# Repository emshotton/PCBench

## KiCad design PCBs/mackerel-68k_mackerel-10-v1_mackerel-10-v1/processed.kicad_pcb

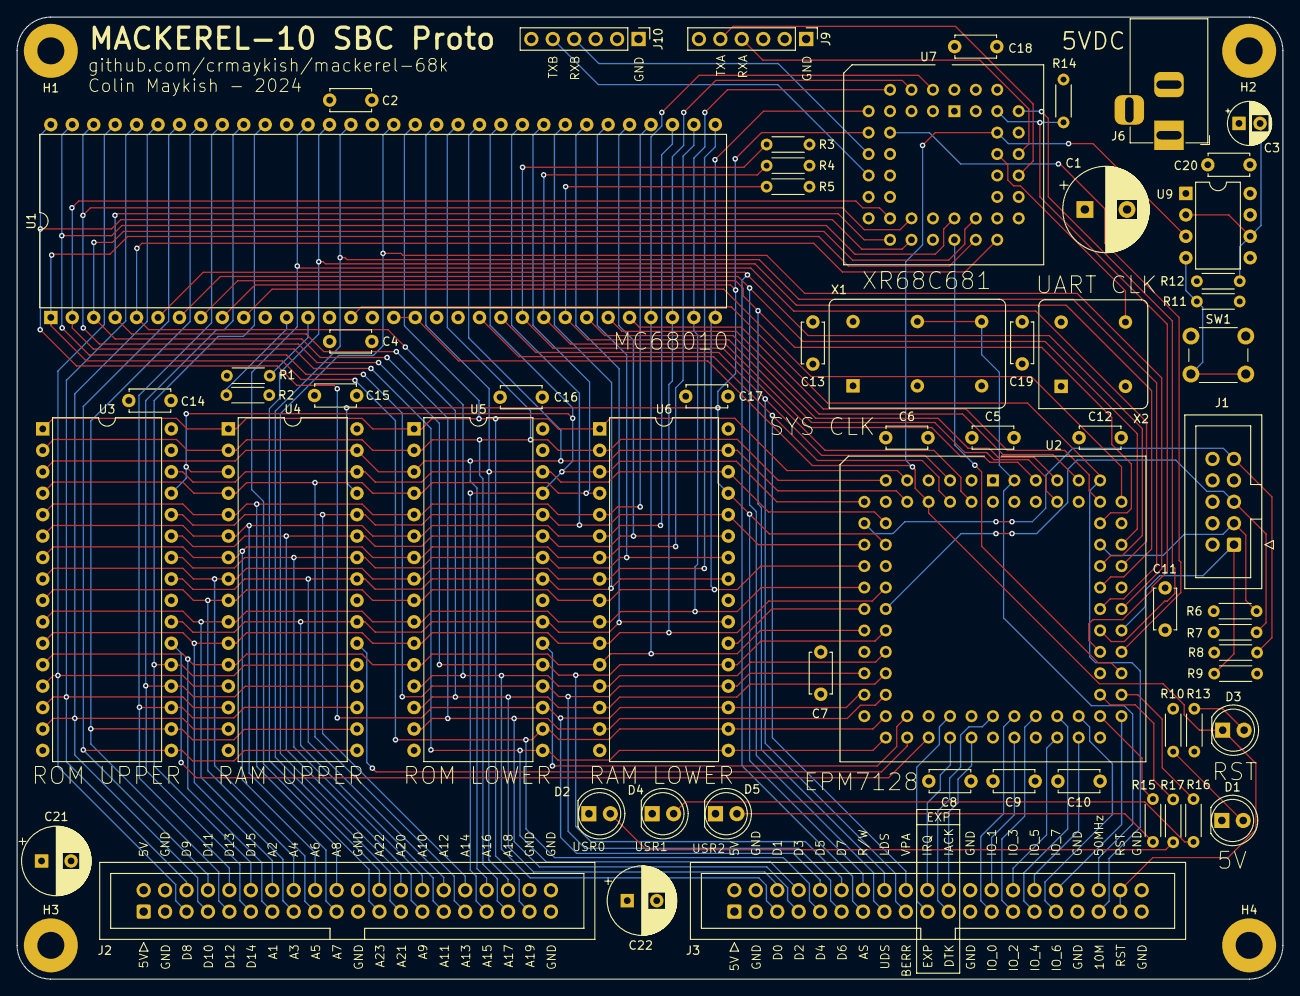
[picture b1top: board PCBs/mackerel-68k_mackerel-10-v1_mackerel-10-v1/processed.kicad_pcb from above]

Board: 4 copper layers, 150.0 x 114.0 mm, 65 parts (0 on the bottom side), 98 nets.

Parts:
C1: 1000uF; CP_Radial_D10.0mm_P5.00mm
C2, C4, C5, C6, C7, C8, C9, C10, C11, C12, C13, C14, C15, C16, C17, C18, C19, C20: 0.1uF; C_Disc_D4.7mm_W2.5mm_P5.00mm
C3: C_Polarized; CP_Radial_D5.0mm_P2.50mm
C21, C22: 1000uF; CP_Radial_D8.0mm_P3.50mm
D1, D2, D3, D4, D5: LED; LED_D5.0mm
H1, H2, H3, H4: MountingHole_Pad; MountingHole_3.2mm_M3_Pad
J1: Conn_02x05_Odd_Even; IDC-Header_2x05_P2.54mm_Vertical
J2, J3: Conn_02x20_Odd_Even; IDC-Header_2x20_P2.54mm_Vertical
J6: Barrel_Jack_MountingPin; BarrelJack_Horizontal
J9, J10: Conn_01x06; PinHeader_1x06_P2.54mm_Vertical
R1, R2, R3, R4, R5, R6, R7, R8, R9, R10, R11, R12, R13, R14, R15, R16, R17: R; R_Axial_DIN0204_L3.6mm_D1.6mm_P5.08mm_Horizontal
SW1: SW_Push; SW_PUSH_6mm_H5mm
U1: 68010D; DIP-64_W22.86mm
U2: PLCC-84_THT-Socket
U3, U5: SST39SF040; DIP-32_W15.24mm
U4, U6: AS6C4008-55PCN; DIP-32_W15.24mm
U7: XR68C681; PLCC-44_THT-Socket
U9: NE555P; DIP-8_W7.62mm
X1: 50MHz; Oscillator_DIP-14
X2: 3.6864MHz; Oscillator_DIP-8

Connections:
+5V: C1.1, C2.1, C3.1, C4.1, C5.1, C6.1, C7.1, C8.1, C9.1, C10.1, C11.1, C12.1, C13.1, C14.1, C15.1, C16.1, C17.1, C18.1, C19.1, C20.1, C21.1, C22.1, J1.4, J2.1, J2.2, J3.1, J3.2, J6.1, R1.1, R2.1, R3.1, R4.1, R5.1, R6.1, R7.1, R8.1, R10.1, R11.1, R13.1, R14.2, U1.14 (VCC), U1.49 (VCC), U2.3 (VCCINT), U2.13 (VCCIO), U2.26 (VCCIO), U2.38 (VCCIO), U2.43 (VCCINT), U2.53 (VCCIO), U2.66 (VCCIO), U2.78 (VCCIO), U3.31 (PGM), U3.32 (VCC), U4.32 (VCC), U5.31 (PGM), U5.32 (VCC), U6.32 (VCC), U7.44 (VCC), U9.8 (VCC), X1.14 (Vcc), X2.8 (Vcc)
A1: J2.13, U1.29 (A1), U2.24 (IO), U3.12 (A0), U4.12 (A0), U5.12 (A0), U6.12 (A0), U7.2 (A1)
A2: J2.14, U1.30 (A2), U2.21 (IO), U3.11 (A1), U4.11 (A1), U5.11 (A1), U6.11 (A1), U7.4 (A2)
A3: J2.15, U1.31 (A3), U2.20 (IO), U3.10 (A2), U4.10 (A2), U5.10 (A2), U6.10 (A2), U7.6 (A3)
A4: J2.16, U1.32 (A4), U2.18 (IO), U3.9 (A3), U4.9 (A3), U5.9 (A3), U6.9 (A3), U7.7 (A4)
A5: J2.17, U1.33 (A5), U3.8 (A4), U4.8 (A4), U5.8 (A4), U6.8 (A4)
A6: J2.18, U1.34 (A6), U3.7 (A5), U4.7 (A5), U5.7 (A5), U6.7 (A5)
A7: J2.19, U1.35 (A7), U3.6 (A6), U4.6 (A6), U5.6 (A6), U6.6 (A6)
A8: J2.20, U1.36 (A8), U3.5 (A7), U4.5 (A7), U5.5 (A7), U6.5 (A7)
A9: J2.27, U1.37 (A9), U3.27 (A8), U4.27 (A8), U5.27 (A8), U6.27 (A8)
A10: J2.28, U1.38 (A10), U3.26 (A9), U4.26 (A9), U5.26 (A9), U6.26 (A9)
A11: J2.29, U1.39 (A11), U3.23 (A10), U4.23 (A10), U5.23 (A10), U6.23 (A10)
A12: J2.30, U1.40 (A12), U3.25 (A11), U4.25 (A11), U5.25 (A11), U6.25 (A11)
A13: J2.31, U1.41 (A13), U3.4 (A12), U4.4 (A12), U5.4 (A12), U6.4 (A12)
A14: J2.32, U1.42 (A14), U2.16 (IO), U3.28 (A13), U4.28 (A13), U5.28 (A13), U6.28 (A13)
A15: J2.33, U1.43 (A15), U2.12 (IO), U3.29 (A14), U4.3 (A14), U5.29 (A14), U6.3 (A14)
A16: J2.34, U1.44 (A16), U2.10 (IO), U3.3 (A15), U4.31 (A15), U5.3 (A15), U6.31 (A15)
A17: J2.35, U1.45 (A17), U2.11 (IO), U3.2 (A16), U4.2 (A16), U5.2 (A16), U6.2 (A16)
A18: J2.36, U1.46 (A18), U2.15 (IO), U3.30 (A17), U4.30 (A17), U5.30 (A17), U6.30 (A17)
A19: J2.37, U1.47 (A19), U2.9 (IO), U3.1 (A18), U4.1 (A18), U5.1 (A18), U6.1 (A18)
A20: J2.26, U1.48 (A20), U2.64 (IO)
A21: J2.25, U1.50 (A21), U2.65 (IO)
A22: J2.24, U1.51 (A22), U2.67 (IO)
A23: J2.23, U1.52 (A23), U2.68 (IO)
CLK_CPU: J3.35, U1.15 (CLK), U2.75 (IO)
CLK_SRC: J3.36, U2.83 (GCLK1), X1.8 (OUT)
D0: J3.5, U1.5 (D0), U2.27 (IO), U5.13 (D0), U6.13 (DQ0), U7.28 (D0)
D1: J3.6, U1.4 (D1), U2.29 (IO), U5.14 (D1), U6.14 (DQ1), U7.18 (D1)
D2: J3.7, U1.3 (D2), U2.31 (IO), U5.15 (D2), U6.15 (DQ2), U7.27 (D2)
D3: J3.8, U1.2 (D3), U2.33 (IO), U5.17 (D3), U6.17 (DQ3), U7.19 (D3)
D4: J3.9, U1.1 (D4), U2.34 (IO), U5.18 (D4), U6.18 (DQ4), U7.26 (D4)
D5: J3.10, U1.64 (D5), U2.30 (IO), U5.19 (D5), U6.19 (DQ5), U7.20 (D5)
D6: J3.11, U1.63 (D6), U2.28 (IO), U5.20 (D6), U6.20 (DQ6), U7.25 (D6)
D7: J3.12, U1.62 (D7), U2.25 (IO), U5.21 (D7), U6.21 (DQ7), U7.21 (D7)
D8: J2.5, U1.61 (D8), U3.13 (D0), U4.13 (DQ0)
D9: J2.6, U1.60 (D9), U3.14 (D1), U4.14 (DQ1)
D10: J2.7, U1.59 (D10), U3.15 (D2), U4.15 (DQ2)
D11: J2.8, U1.58 (D11), U3.17 (D3), U4.17 (DQ3)
D12: J2.9, U1.57 (D12), U3.18 (D4), U4.18 (DQ4)
D13: J2.10, U1.56 (D13), U3.19 (D5), U4.19 (DQ5)
D14: J2.11, U1.55 (D14), U3.20 (D6), U4.20 (DQ6)
D15: J2.12, U1.54 (D15), U3.21 (D7), U4.21 (DQ7)
FC0: U1.28 (FC0), U2.76 (IO)
FC1: U1.27 (FC1), U2.77 (IO)
FC2: U1.26 (FC2), U2.79 (IO)
GND: C1.2, C2.2, C4.2, C5.2, C6.2, C7.2, C8.2, C9.2, C10.2, C11.2, C12.2, C13.2, C14.2, C15.2, C16.2, C17.2, C18.2, C19.2, C20.2, C21.2, C22.2, D1.1 (K), D2.1 (K), D4.1 (K), D5.1 (K), H1.1, H2.1, H3.1, H4.1, J1.2, J1.10, J2.3, J2.4, J2.21, J2.22, J2.38, J2.39, J2.40, J3.3, J3.4, J3.23, J3.24, J3.33, J3.34, J3.39, J3.40, J6.2, J9.1, J10.1, R9.2, R12.2, SW1.1, U1.16 (GND), U1.53 (GND), U2.1 (GCLRn), U2.2 (OE2/GCLK2), U2.7 (GND), U2.19 (GND), U2.32 (GND), U2.42 (GND), U2.47 (GND), U2.59 (GND), U2.72 (GND), U2.82 (GND), U2.84 (OE1), U3.16 (GND), U3.24 (OE), U4.16 (VSS), U4.24 (OE#), U5.16 (GND), U5.24 (OE), U6.16 (VSS), U6.24 (OE#), U7.3 (IP3), U7.5 (IP1), U7.8 (IP0), U7.22 (GND), U7.40 (IP2), U7.42 (IP5), U7.43 (IP4), U9.1 (GND), X1.7 (GND), X2.4 (GND)
GPIO_0: J3.25, U2.46 (IO)
GPIO_1: J3.26, U2.45 (IO)
GPIO_2: J3.27, U2.48 (IO)
GPIO_3: J3.28, U2.49 (IO)
GPIO_4: J3.29, U2.50 (IO)
GPIO_5: J3.30, U2.51 (IO)
GPIO_6: J3.31, U2.52 (IO)
GPIO_7: J3.32, U2.54 (IO)
unnamed: D1.2 (A), R10.2
unnamed: D3.2 (A), R13.2
unnamed: R15.1, U2.55 (IO)
unnamed: R16.1, U2.56 (IO)
unnamed: R17.1, U2.57 (IO)
unnamed: R2.2, U1.12 (BGACK)
unnamed: R1.2, U1.13 (BR)
unnamed: U7.36 (X1/CLK), X2.5 (OUT)
unnamed: R11.2, SW1.2, U9.4 (R)
unnamed: C3.2, R12.1, U9.2 (TR), U9.6 (THR)
RXA: J9.4, U7.35 (RXDA)
RXB: J10.4, U7.11 (RXDB)
R/W: J3.14, U1.9 (R/W), U2.17 (IO), U4.29 (WE#), U6.29 (WE#), U7.9 (/RW)
TCK: J1.1, R9.1, U2.62 (TCK)
TDI: J1.9, R8.2, U2.14 (TDI)
TDO: J1.3, R6.2, U2.71 (TDO)
TMS: J1.5, R7.2, U2.23 (TMS)
TXA: J9.5, U7.33 (TXDA)
TXB: J10.5, U7.13 (TXDB)
USR0: D5.2 (A), R15.2
USR1: D4.2 (A), R16.2
USR2: D2.2 (A), R17.2
/AS: J3.13, U1.6 (AS), U2.69 (IO)
/BERR: J3.17, U1.22 (BERR), U2.5 (IO)
/DTACK: U1.10 (DTACK), U2.74 (IO)
/DTACK_DUART: U2.60 (IO), U7.10 (/DTACK)
/DTACK_EXP: J3.21, U2.44 (IO)
/DUART: U2.63 (IO), U7.39 (CS)
/EXP: J3.19, U2.40 (IO)
/IACK_DUART: R14.1, U2.61 (IO), U7.41 (/IACK)
/IACK_EXP: J3.22, U2.41 (IO)
/IPL0: R5.2, U1.25 (IPL0), U2.80 (IO)
/IPL1: R4.2, U1.24 (IPL1), U2.81 (IO)
/IPL2: R3.2, U1.23 (IPL2), U2.4 (IO)
/IRQ_DUART: U2.58 (IO), U7.24 (INTR)
/IRQ_EXP: J3.20, U2.39 (IO)
/LDS: J3.16, U1.8 (LDS), U2.73 (IO)
/RESET: D3.1 (K), J3.37, J3.38, U1.17 (HALT), U1.18 (RESET), U2.8 (IO), U7.38 (/RESET), U9.3 (Q)
/ROM_LOWER: U2.36 (IO), U5.22 (CE)
/ROM_UPPER: U2.37 (IO), U3.22 (CE)
/SRAM_LOWER: U2.22 (IO), U6.22 (CE#)
/SRAM_UPPER: U2.35 (IO), U4.22 (CE#)
/UDS: J3.15, U1.7 (UDS), U2.70 (IO)
/VPA: J3.18, U1.21 (VPA), U2.6 (IO)

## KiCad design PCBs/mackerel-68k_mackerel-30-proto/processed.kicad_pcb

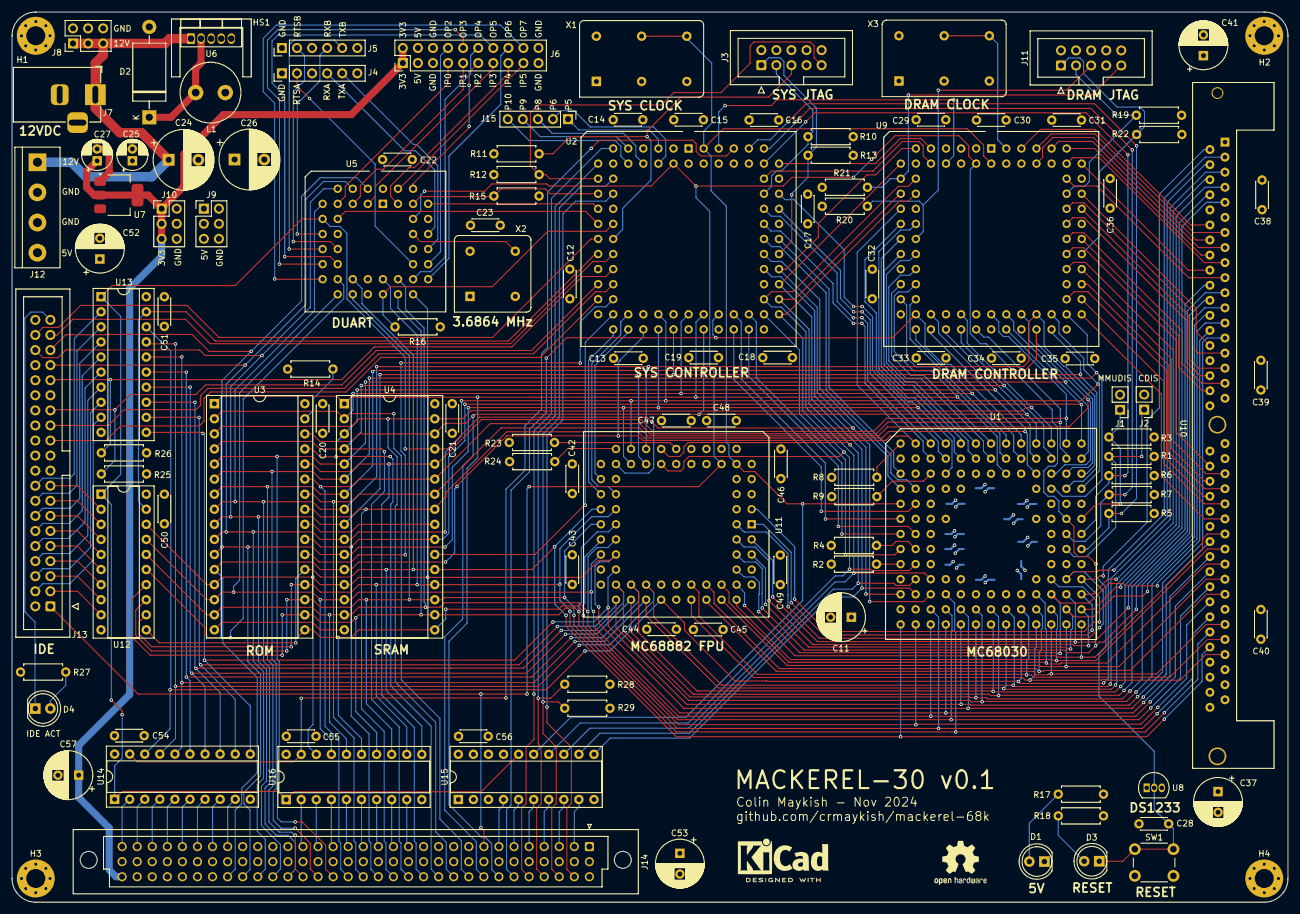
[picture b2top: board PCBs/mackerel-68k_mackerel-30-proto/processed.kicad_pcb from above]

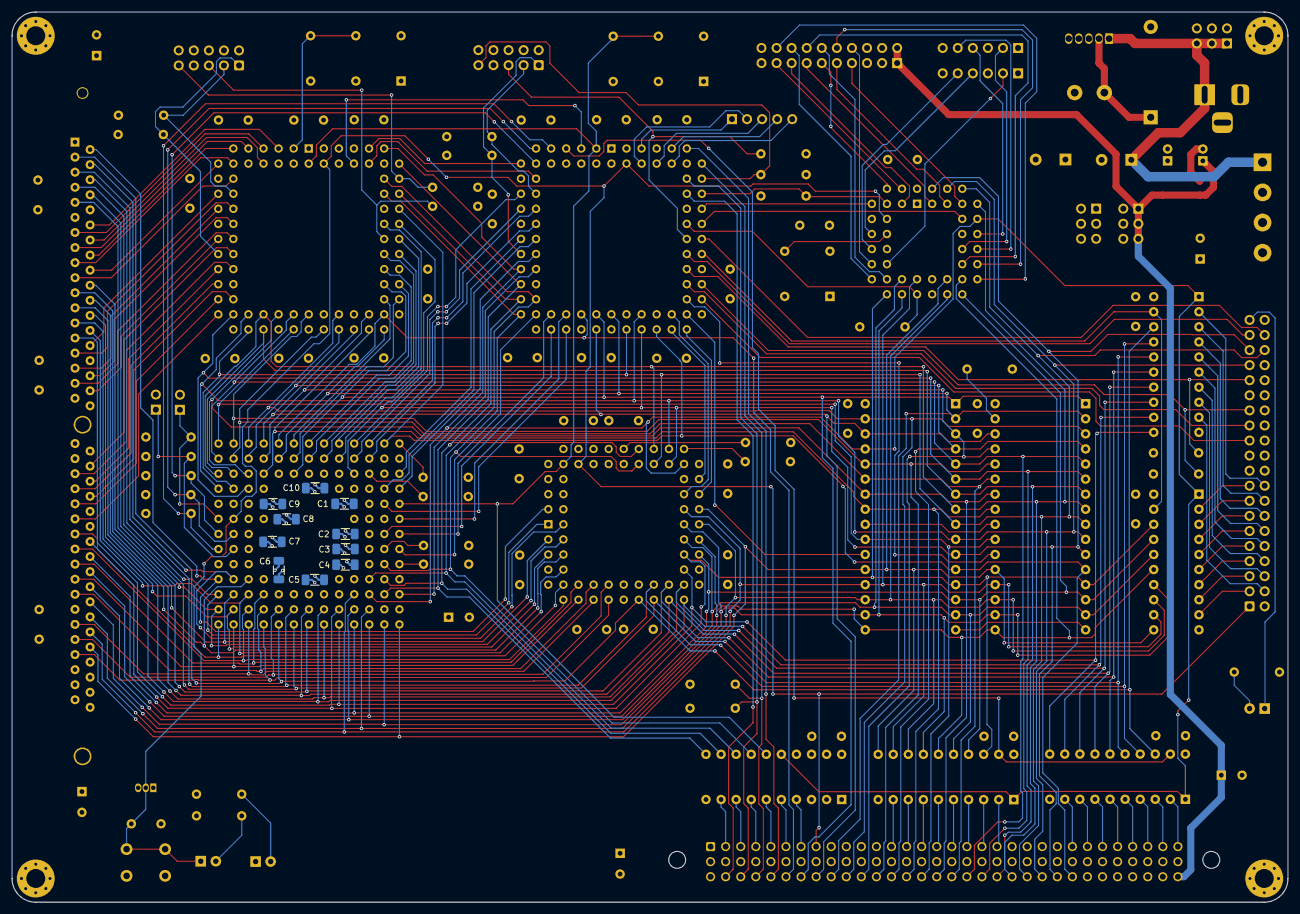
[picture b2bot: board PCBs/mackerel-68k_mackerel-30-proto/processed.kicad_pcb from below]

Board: 4 copper layers, 215.0 x 150.0 mm, 131 parts (10 on the bottom side), 217 nets.

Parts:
C1, C2, C3, C4, C5, C6, C7, C8, C9, C10: 0.1uF; C_1206_3216Metric_Pad1.33x1.80mm_HandSolder
C11, C37, C41, C52, C53, C57: 470uF; CP_Radial_D8.0mm_P3.50mm
C12, C13, C14, C15, C16, C17, C18, C19, C20, C21, C22, C23, C29, C30, C31, C32, C33, C34, C35, C36, C38, C39, C40, C42, C43, C44, C45, C46, C47, C48, C49, C54, C55, C56: 0.1uF; C_Disc_D4.3mm_W1.9mm_P5.00mm
C24, C26: 1000uF; CP_Radial_D10.0mm_P5.00mm
C25, C27: 10uF; CP_Radial_D5.0mm_P2.00mm
C28: 0.01uF; C_Disc_D4.3mm_W1.9mm_P5.00mm
C50, C51: C; C_Disc_D4.3mm_W1.9mm_P5.00mm
D1, D3, D4: LED; LED_D5.0mm
D2: 1N5822; D_DO-27_P15.24mm_Horizontal
H1, H2, H3, H4: MountingHole_Pad; MountingHole_3.2mm_M3_Pad_Via
HS1: Heatsink; Heatsink_Stonecold_HS-S02_13.21x9.53mm
J1, J2: Conn_01x02; PinHeader_1x02_P2.54mm_Vertical
J3, J11: Conn_02x05_Odd_Even; IDC-Header_2x05_P2.54mm_Vertical
J4, J5: Conn_01x06; PinHeader_1x06_P2.54mm_Vertical
J6: Conn_02x10_Odd_Even; PinHeader_2x10_P2.54mm_Vertical
J7: Barrel_Jack_MountingPin; BarrelJack_Horizontal
J8, J9, J10: Conn_02x03_Odd_Even; PinHeader_2x03_P2.54mm_Vertical
J12: Screw_Terminal_01x04; TerminalBlock_bornier-4_P5.08mm
J13: Conn_02x20_Odd_Even; IDC-Header_2x20_P2.54mm_Vertical
J14: DIN41612_03x32_ABC; DIN41612_C_3x32_Female_Vertical_THT
J15: Conn_01x05; PinHeader_1x05_P2.54mm_Vertical
L1: 100uH; L_Radial_D10.0mm_P5.00mm_Fastron_07M
R1, R2, R3, R4, R5, R6, R7, R8, R9, R14, R23, R24, R25, R26, R28, R29: 4k7; R_Axial_DIN0207_L6.3mm_D2.5mm_P7.62mm_Horizontal
R10, R11, R12, R13, R15, R16, R19, R20, R21, R22: R; R_Axial_DIN0207_L6.3mm_D2.5mm_P7.62mm_Horizontal
R17, R18: 1k; R_Axial_DIN0207_L6.3mm_D2.5mm_P7.62mm_Horizontal
R27: 470; R_Axial_DIN0207_L6.3mm_D2.5mm_P7.62mm_Horizontal
SW1: SW_Push; SW_PUSH_6mm_H5mm
U1: MC68030RC; PGA169
U2, U9: EPM7128; PLCC-84_THT-Socket
U3: SST39SF040; DIP-32_W15.24mm_Socket
U4: AS6C4008-55PCN; DIP-32_W15.24mm_Socket
U5: XR68C681; PLCC-44_THT-Socket
U6: LM2576T-5; TO-220-5_Vertical
U7: AMS1117-3.3; SOT-223-3_TabPin2
U8: DS1233; TO-92L_Inline
U10: SIMM72; SIMM-72
U11: MC68882; PLCC-68_THT-Socket
U12, U13, U14, U15, U16: 74HC245; DIP-20_W7.62mm_Socket
X1, X3: CXO_DIP14; Oscillator_DIP-14
X2: 3.6864MHz; Oscillator_DIP-8

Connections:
+3.3V: C27.1, C57.1, J6.1, J6.2, J10.1, J10.3, J10.5, J14.c32, U7.2 (VO)
+5V: C1.1, C2.1, C3.1, C4.1, C5.1, C6.1, C7.1, C8.1, C9.1, C10.1, C11.1, C12.1, C13.1, C14.1, C15.1, C16.1, C17.1, C18.1, C19.1, C20.1, C21.1, C22.1, C23.1, C25.1, C26.1, C29.1, C30.1, C31.1, C32.1, C33.1, C34.1, C35.1, C36.1, C37.1, C38.1, C39.1, C40.1, C41.1, C42.1, C43.1, C44.1, C45.1, C46.1, C47.1, C48.1, C49.1, C50.1, C51.1, C52.1, C53.1, C54.1, C55.1, C56.1, J3.4, J6.3, J6.4, J9.1, J9.3, J9.5, J11.4, J12.4, J14.a1, J14.c1, L1.2, R1.1, R2.1, R3.1, R4.1, R5.1, R6.1, R7.1, R8.1, R9.1, R10.1, R11.1, R12.1, R14.1, R15.2, R16.2, R17.1, R18.1, R19.1, R20.1, R21.1, R23.1, R24.1, R27.1, R28.2, R29.2, U1.C6 (VCC), U1.D4 (VCC), U1.D10 (VCC), U1.F2 (VCC), U1.F11 (VCC), U1.H3 (VCC), U1.H11 (VCC), U1.K4 (VCC), U1.K10 (VCC), U1.L6 (VCC), U2.3 (VCCINT), U2.13 (VCCIO), U2.26 (VCCIO), U2.38 (VCCIO), U2.43 (VCCINT), U2.53 (VCCIO), U2.66 (VCCIO), U2.78 (VCCIO), U3.32 (VCC), U4.32 (VCC), U5.44 (VCC), U6.4 (FB), U7.3 (VI), U8.3 (VCC), U9.3 (VCCINT), U9.13 (VCCIO), U9.26 (VCCIO), U9.38 (VCCIO), U9.43 (VCCINT), U9.53 (VCCIO), U9.66 (VCCIO), U9.78 (VCCIO), U10.10 (VCC), U10.30 (VCC), U10.59 (VCC), U11.10 (VCC), U11.16 (VCC), U11.17 (VCC), U11.27 (VCC), U11.43 (VCC), U11.52 (VCC), U11.53 (VCC), U11.61 (VCC), U12.20 (VCC), U13.20 (VCC), U14.20 (VCC), U15.20 (VCC), U16.20 (VCC), X1.14 (Vcc), X2.8 (Vcc), X3.14 (Vcc)
+12V: C24.1, J7.1, J8.1, J8.3, J8.5, J12.1, U6.1 (VIN)
A0: J14.c25, U1.A2 (A0), U2.37 (IO), U3.12 (A0), U4.12 (A0), U9.18 (IO)
A1: J13.35, J14.c24, U1.C4 (A1), U2.39 (IO), U3.11 (A1), U4.11 (A1), U5.2 (A1), U9.20 (IO), U11.25 (A1)
A2: J13.33, J14.c23, U1.D13 (A2), U2.40 (IO), U3.10 (A2), U4.10 (A2), U5.4 (A2), U9.52 (IO), U11.24 (A2)
A3: J13.36, J14.c22, U1.D12 (A3), U2.41 (IO), U3.9 (A3), U4.9 (A3), U5.6 (A3), U9.51 (IO), U11.23 (A3)
A4: J14.c21, U1.C13 (A4), U3.8 (A4), U4.8 (A4), U5.7 (A4), U9.50 (IO), U11.22 (A4)
A5: J14.c20, U1.C12 (A5), U3.7 (A5), U4.7 (A5), U9.49 (IO)
A6: J14.c19, U1.D11 (A6), U3.6 (A6), U4.6 (A6), U9.55 (IO)
A7: J14.c18, U1.B13 (A7), U3.5 (A7), U4.5 (A7), U9.46 (IO)
A8: J14.c17, U1.B12 (A8), U3.27 (A8), U4.27 (A8), U9.41 (IO)
A9: J14.c16, U1.C11 (A9), U3.26 (A9), U4.26 (A9), U9.48 (IO)
A10: J14.c15, U1.A13 (A10), U3.23 (A10), U4.23 (A10), U9.45 (IO)
A11: J14.c14, U1.C10 (A11), U3.25 (A11), U4.25 (A11), U9.35 (IO)
A12: J14.c13, U1.B11 (A12), U3.4 (A12), U4.4 (A12), U9.39 (IO)
A13: J14.c12, U1.A12 (A13), U3.28 (A13), U4.28 (A13), U9.44 (IO)
A14: J14.c11, U1.B10 (A14), U3.29 (A14), U4.3 (A14), U9.36 (IO)
A15: J14.c10, U1.A11 (A15), U3.3 (A15), U4.31 (A15), U9.40 (IO)
A16: J14.c9, U1.B9 (A16), U2.44 (IO), U3.2 (A16), U4.2 (A16), U9.33 (IO)
A17: J14.c8, U1.A10 (A17), U2.45 (IO), U3.30 (A17), U4.30 (A17), U9.37 (IO)
A18: J14.c7, U1.C8 (A18), U2.46 (IO), U3.1 (A18), U4.1 (A18), U9.29 (IO)
A19: J14.c6, U1.A9 (A19), U2.48 (IO), U9.34 (IO)
A20: U1.B8 (A20), U9.30 (IO)
A21: U1.A8 (A21), U9.31 (IO)
A22: U1.B7 (A22), U9.27 (IO)
A23: U1.A7 (A23), U9.28 (IO)
A24: U1.A6 (A24), U9.25 (IO)
A25: U1.B6 (A25), U9.24 (IO)
A26: U1.A5 (A26), U9.22 (IO)
A27: U1.B5 (A27), U9.21 (IO)
A28: U1.A4 (A28), U2.70 (IO)
A29: U1.B4 (A29), U2.68 (IO)
A30: U1.A3 (A30), U2.69 (IO)
A31: U1.B3 (A31), U2.67 (IO)
CLK_CPU: U1.E1 (CLK), U2.83 (GCLK1), U9.2 (OE2/GCLK2), U11.11 (CLK), U15.15 (B3), X1.8 (OUT)
CLK_DRAM: U9.83 (GCLK1), X3.8 (OUT)
CS_EXP: J14.c5, U2.11 (IO)
D0: U1.K13 (D0), U10.2 (D0), U11.3 (D0)
D1: U1.K12 (D1), U10.4 (D1), U11.2 (D1)
D2: U1.L13 (D2), U10.6 (D2), U11.1 (D2)
D3: U1.M13 (D3), U10.8 (D3), U11.68 (D3)
D4: U1.L12 (D4), U10.20 (D4), U11.67 (D4)
D5: U1.K11 (D5), U10.22 (D5), U11.66 (D5)
D6: U1.M12 (D6), U10.24 (D6), U11.65 (D6)
D7: U1.L11 (D7), U10.26 (D7), U11.64 (D7)
D8: U1.N13 (D8), U10.49 (D8), U11.62 (D8)
D9: U1.M11 (D9), U10.51 (D9), U11.60 (D9)
D10: U1.L10 (D10), U10.53 (D10), U11.59 (D10)
D11: U1.N12 (D11), U10.55 (D11), U11.58 (D11)
D12: U1.M10 (D12), U10.57 (D12), U11.57 (D12)
D13: U1.N11 (D13), U10.61 (D13), U11.56 (D13)
D14: U1.M9 (D14), U10.63 (D14), U11.55 (D14)
D15: U1.N10 (D15), U10.65 (D15), U11.54 (D15)
D16: U1.N9 (D16), U10.3 (D16), U11.50 (D16), U13.18 (B0), U14.18 (B0)
D17: U1.M8 (D17), U10.5 (D17), U11.49 (D17), U13.17 (B1), U14.17 (B1)
D18: U1.N8 (D18), U10.7 (D18), U11.48 (D18), U13.16 (B2), U14.16 (B2)
D19: U1.N7 (D19), U10.9 (D19), U11.47 (D19), U13.15 (B3), U14.15 (B3)
D20: U1.M7 (D20), U10.21 (D20), U11.46 (D20), U13.14 (B4), U14.14 (B4)
D21: U1.N6 (D21), U10.23 (D21), U11.45 (D21), U13.13 (B5), U14.13 (B5)
D22: U1.M6 (D22), U10.25 (D22), U11.44 (D22), U13.12 (B6), U14.12 (B6)
D23: U1.N5 (D23), U10.27 (D23), U11.42 (D23), U13.11 (B7), U14.11 (B7)
D24: U1.M5 (D24), U3.13 (D0), U4.13 (DQ0), U5.28 (D0), U10.50 (D24), U11.40 (D24), U12.18 (B0), U16.18 (B0)
D25: U1.N4 (D25), U3.14 (D1), U4.14 (DQ1), U5.18 (D1), U10.52 (D25), U11.39 (D25), U12.17 (B1), U16.17 (B1)
D26: U1.N3 (D26), U3.15 (D2), U4.15 (DQ2), U5.27 (D2), U10.54 (D26), U11.38 (D26), U12.16 (B2), U16.16 (B2)
D27: U1.M4 (D27), U3.17 (D3), U4.17 (DQ3), U5.19 (D3), U10.56 (D27), U11.37 (D27), U12.15 (B3), U16.15 (B3)
D28: U1.N2 (D28), U3.18 (D4), U4.18 (DQ4), U5.26 (D4), U10.58 (D28), U11.36 (D28), U12.14 (B4), U16.14 (B4)
D29: U1.M3 (D29), U3.19 (D5), U4.19 (DQ5), U5.20 (D5), U10.60 (D29), U11.35 (D29), U12.13 (B5), U16.13 (B5)
D30: U1.L4 (D30), U3.20 (D6), U4.20 (DQ6), U5.25 (D6), U10.62 (D30), U11.34 (D30), U12.12 (B6), U16.12 (B6)
D31: U1.N1 (D31), U3.21 (D7), U4.21 (DQ7), U5.21 (D7), U10.64 (D31), U11.33 (D31), U12.11 (B7), U16.11 (B7)
DRAM_A0: U9.81 (IO), U10.12 (A0)
DRAM_A1: U9.79 (IO), U10.13 (A1)
DRAM_A2: U9.80 (IO), U10.14 (A2)
DRAM_A3: U9.77 (IO), U10.15 (A3)
DRAM_A4: U9.75 (IO), U10.16 (A4)
DRAM_A5: U9.76 (IO), U10.17 (A5)
DRAM_A6: U9.74 (IO), U10.18 (A6)
DRAM_A7: U9.70 (IO), U10.28 (A7)
DRAM_A8: U9.68 (IO), U10.31 (A8)
DRAM_A9: U9.67 (IO), U10.32 (A9)
DRAM_A10: U9.73 (IO), U10.19 (A10)
DRAM_A11: U9.69 (IO), U10.29 (A11)
DRAM_WR: U9.54 (IO), U10.47 (/WE)
DTACK_EXP: J14.c4, R28.1, U2.12 (IO)
EXP_AS: J14.a5, U15.6 (A4)
EXP_CLK: J14.a6, U15.5 (A3)
EXP_D16: J14.a32, U14.2 (A0)
EXP_D17: J14.a31, U14.3 (A1)
EXP_D18: J14.a30, U14.4 (A2)
EXP_D19: J14.a29, U14.5 (A3)
EXP_D20: J14.a28, U14.6 (A4)
EXP_D21: J14.a27, U14.7 (A5)
EXP_D22: J14.a26, U14.8 (A6)
EXP_D23: J14.a25, U14.9 (A7)
EXP_D24: J14.a20, U16.2 (A0)
EXP_D25: J14.a19, U16.3 (A1)
EXP_D26: J14.a18, U16.4 (A2)
EXP_D27: J14.a17, U16.5 (A3)
EXP_D28: J14.a16, U16.6 (A4)
EXP_D29: J14.a15, U16.7 (A5)
EXP_D30: J14.a14, U16.8 (A6)
EXP_D31: J14.a13, U16.9 (A7)
EXP_DS: J14.a3, U15.8 (A6)
EXP_RW: J14.a7, U15.4 (A2)
EXP_SIZ0: J14.a2, U15.9 (A7)
EXP_SIZ1: J14.a4, U15.7 (A5)
FC0: U1.D2 (FC0), U2.65 (IO)
FC1: U1.C1 (FC1), U2.64 (IO)
FC2: U1.D1 (FC2), U2.63 (IO)
GND: C1.2, C2.2, C3.2, C4.2, C5.2, C6.2, C7.2, C8.2, C9.2, C10.2, C11.2, C12.2, C13.2, C14.2, C15.2, C16.2, C17.2, C18.2, C19.2, C20.2, C21.2, C22.2, C23.2, C24.2, C25.2, C26.2, C27.2, C28.2, C29.2, C30.2, C31.2, C32.2, C33.2, C34.2, C35.2, C36.2, C37.2, C38.2, C39.2, C40.2, C41.2, C42.2, C43.2, C44.2, C45.2, C46.2, C47.2, C48.2, C49.2, C50.2, C51.2, C52.2, C53.2, C54.2, C55.2, C56.2, C57.2, D1.1 (K), D2.2 (A), H1.1, H2.1, H3.1, H4.1, J1.2, J2.2, J3.2, J3.10, J4.1, J5.1, J6.5, J6.6, J6.19, J6.20, J7.2, J8.2, J8.4, J8.6, J9.2, J9.4, J9.6, J10.2, J10.4, J10.6, J11.2, J11.10, J12.2, J12.3, J13.2, J13.19, J13.22, J13.24, J13.26, J13.30, J13.40, J14.b1, J14.b2, J14.b3, J14.b4, J14.b5, J14.b6, J14.b7, J14.b8, J14.b9, J14.b10, J14.b11, J14.b12, J14.b13, J14.b14, J14.b15, J14.b16, J14.b17, J14.b18, J14.b19, J14.b20, J14.b21, J14.b22, J14.b23, J14.b24, J14.b25, J14.b26, J14.b27, J14.b28, J14.b29, J14.b30, J14.b31, J14.b32, R13.2, R22.2, R25.1, R26.1, SW1.2, U1.C5 (GND), U1.C7 (GND), U1.C9 (GND), U1.E3 (GND), U1.E11 (GND), U1.F3 (GND), U1.G3 (GND), U1.G11 (GND), U1.J3 (GND), U1.J11 (GND), U1.L5 (GND), U1.L7 (GND), U1.L8 (GND), U1.L9 (GND), U2.1 (GCLRn), U2.7 (GND), U2.19 (GND), U2.32 (GND), U2.42 (GND), U2.47 (GND), U2.59 (GND), U2.72 (GND), U2.82 (GND), U2.84 (OE1), U3.16 (GND), U3.24 (OE), U4.16 (VSS), U4.24 (OE#), U5.22 (GND), U6.3 (GND), U6.5 (~ON/OFF), U7.1 (GND), U8.1 (GND), U9.1 (GCLRn), U9.7 (GND), U9.19 (GND), U9.32 (GND), U9.42 (GND), U9.47 (GND), U9.59 (GND), U9.72 (GND), U9.82 (GND), U9.84 (OE1), U10.1 (GND), U10.39 (GND), U10.72 (GND), U11.4 (/SENSE), U11.5 (GND), U11.6 (GND), U11.7 (GND), U11.8 (GND), U11.9 (GND), U11.12 (GND), U11.14 (GND), U11.19 (GND), U11.30 (GND), U11.41 (GND), U11.51 (GND), U11.63 (GND), U12.10 (GND), U13.10 (GND), U14.10 (GND), U15.1 (A->B), U15.10 (GND), U15.17 (B1), U15.18 (B0), U15.19 (CE), U16.10 (GND), X1.7 (GND), X2.4 (GND), X3.7 (GND)
IACK_EXP: J14.c2, U2.17 (IO)
IDE_D0: J13.17, U12.2 (A0)
IDE_D1: J13.15, U12.3 (A1)
IDE_D2: J13.13, U12.4 (A2)
IDE_D3: J13.11, U12.5 (A3)
IDE_D4: J13.9, U12.6 (A4)
IDE_D5: J13.7, U12.7 (A5)
IDE_D6: J13.5, U12.8 (A6)
IDE_D7: J13.3, U12.9 (A7)
IDE_D8: J13.4, U13.9 (A7)
IDE_D9: J13.6, U13.8 (A6)
IDE_D10: J13.8, U13.7 (A5)
IDE_D11: J13.10, U13.6 (A4)
IDE_D12: J13.12, U13.5 (A3)
IDE_D13: J13.14, U13.4 (A2)
IDE_D14: J13.16, U13.3 (A1)
IDE_D15: J13.18, U13.2 (A0)
IDE_INT: J13.31, R26.2, U2.27 (IO)
IDE_RDY: J13.27, R25.2, U2.28 (IO)
IP0: J6.7, U5.8 (IP0)
IP1: J6.9, U5.5 (IP1)
IP2: J6.11, U5.40 (IP2)
IP3: J6.13, U5.3 (IP3)
IP4: J6.15, U5.43 (IP4)
IP5: J6.17, U5.42 (IP5)
IRQ_EXP: J14.c3, R29.1, U2.15 (IO)
unnamed: D1.2 (A), R17.2
unnamed: D2.1 (K), L1.1, U6.2 (OUT)
unnamed: D3.2 (A), R18.2
unnamed: D4.2 (A), R27.2
unnamed: D4.1 (K), J13.39
unnamed: J1.1, R3.2, U1.F13 (/MMUDIS)
unnamed: J2.1, R1.2, U1.H12 (/CDIS)
unnamed: J15.1, U2.5 (IO)
unnamed: J15.2, U2.6 (IO)
unnamed: J15.3, U2.8 (IO)
unnamed: J15.4, U2.9 (IO)
unnamed: J15.5, U2.10 (IO)
unnamed: R9.2, U1.C3 (/BGACK)
unnamed: R8.2, U1.A1 (/BR)
unnamed: R2.2, U1.J1 (/CBACK)
unnamed: R4.2, U1.H2 (/HALT)
unnamed: R14.2, U3.31 (PGM)
unnamed: U5.36 (X1/CLK), X2.5 (OUT)
unnamed: R24.2, U11.26 (A0)
unnamed: R23.2, U11.18 (/SIZE)
OP2: J6.8, U5.31 (OP2)
OP3: J6.10, U5.15 (OP3)
OP4: J6.12, U5.30 (OP4)
OP5: J6.14, U5.16 (OP5)
OP6: J6.16, U5.29 (OP6)
OP7: J6.18, U5.17 (OP7)
RXA: J4.4, U5.35 (RXDA)
RXB: J5.4, U5.11 (RXDB)
R/W: U1.L3 (R/W), U2.60 (IO), U4.29 (WE#), U5.9 (/RW), U9.11 (IO), U11.28 (R/W), U12.1 (A->B), U13.1 (A->B), U14.1 (A->B), U15.16 (B2), U16.1 (A->B)
SIZ0: U1.L2 (SIZ0), U2.58 (IO), U9.12 (IO), U15.11 (B7)
SIZ1: U1.K3 (SIZ1), U2.57 (IO), U9.15 (IO), U15.13 (B5)
TCK: J3.1, R13.1, U2.62 (TCK)
TCK_DRAM: J11.1, R22.1, U9.62 (TCK)
TDI: J3.9, R12.2, U2.14 (TDI)
TDI_DRAM: J11.9, R21.2, U9.14 (TDI)
TDO: J3.3, R10.2, U2.71 (TDO)
TDO_DRAM: J11.3, R19.2, U9.71 (TDO)
TMS: J3.5, R11.2, U2.23 (TMS)
TMS_DRAM: J11.5, R20.2, U9.23 (TMS)
TXA: J4.5, U5.33 (TXDA)
TXB: J5.5, U5.13 (TXDB)
/AS: U1.J2 (/AS), U2.54 (IO), U9.17 (IO), U11.21 (/AS), U15.14 (B4)
/AVEC: U1.E2 (/AVEC), U2.49 (IO)
/BERR: U1.H1 (/BERR), U2.55 (IO)
/CAS0: U9.63 (IO), U10.40 (/CAS0)
/CAS1: U9.58 (IO), U10.43 (/CAS1)
/CAS2: U9.61 (IO), U10.41 (/CAS2)
/CAS3: U9.60 (IO), U10.42 (/CAS3)
/CIIN: U1.L1 (/CIIN), U2.61 (IO)
/CS_DRAM: U2.73 (IO), U9.10 (IO)
/CS_DUART: U2.18 (IO), U5.39 (CS)
/CS_FPU: U2.35 (IO), U11.29 (/CS)
/CS_ROM: U2.31 (IO), U3.22 (CE)
/CS_SRAM: U2.34 (IO), U4.22 (CE#)
/DS: U1.K2 (/DS), U2.56 (IO), U9.16 (IO), U11.20 (/DS), U15.12 (B6)
/DSACK0: U1.F1 (/DSACK0), U2.50 (IO)
/DSACK0_DRAM: U2.74 (IO), U9.9 (IO)
/DSACK0_FPU: U2.33 (IO), U11.31 (/DSACK0)
/DSACK1: U1.G2 (/DSACK1), U2.51 (IO)
/DSACK1_DRAM: U2.81 (IO), U9.8 (IO)
/DSACK1_FPU: U2.36 (IO), U11.32 (/DSACK1)
/DTACK_DUART: U2.20 (IO), U5.10 (/DTACK)
/EXP_BUF: U2.79 (IO), U14.19 (CE), U16.19 (CE)
/IACK_DUART: R15.1, U2.16 (IO), U5.41 (/IACK)
/IDE_BUF: U2.24 (IO), U12.19 (CE), U13.19 (CE)
/IDE_CS0: J13.37, U2.25 (IO)
/IDE_CS1: J13.38, U2.22 (IO)
/IDE_RD: J13.25, U2.29 (IO)
/IDE_WR: J13.23, U2.30 (IO)
/IPL0: R5.2, U1.H13 (/IPL0), U2.77 (IO)
/IPL1: R6.2, U1.G13 (/IPL1), U2.76 (IO)
/IPL2: R7.2, U1.G12 (/IPL2), U2.75 (IO)
/IRQ_DUART: R16.1, U2.21 (IO), U5.24 (INTR)
/RAS0: U9.57 (IO), U10.44 (/RAS0)
/RAS1: U9.64 (IO), U10.34 (/RAS2)
/RAS2: U9.56 (IO), U10.45 (/RAS1)
/RAS3: U9.65 (IO), U10.33 (/RAS3)
/RESET: C28.1, D3.1 (K), J13.1, J14.a8, SW1.1, U1.F12 (/RESET), U2.4 (IO), U5.38 (/RESET), U8.2 (/RESET), U9.4 (IO), U11.13 (/RESET)
/RTSA: J4.2, U5.32 (OP0)
/RTSB: J5.2, U5.14 (OP1)
/STERM: U1.G1 (/STERM), U2.52 (IO)

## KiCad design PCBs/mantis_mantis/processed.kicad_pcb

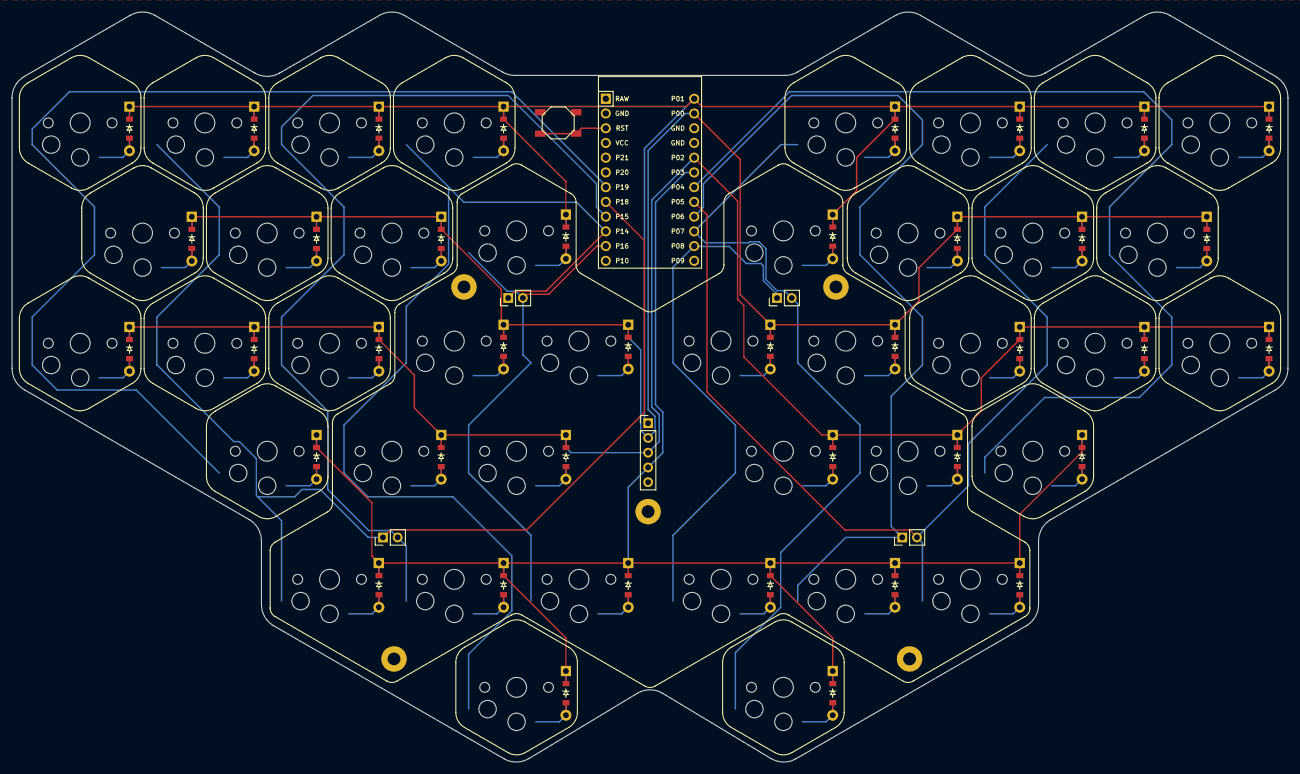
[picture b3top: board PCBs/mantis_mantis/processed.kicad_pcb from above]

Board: 2 copper layers, 220.0 x 129.3 mm, 82 parts (0 on the bottom side), 56 nets.

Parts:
B1: SW_TACT_ALPS_SKQGABE010
D1, D2, D3, D4, D5, D6, D7, D8, D9, D10, D11, D12, D13, D14, D15, D16, D17, D18, D19, D20, D21, D22, D23, D24, D25, D26, D27, D28, D29, D30, D31, D32, D33, D34, D35, D36, D37, D38, D39, D40: ComboDiode
MCU1: ProMicro
S1, S2, S3, S4, S5, S6, S7, S8, S9, S10, S11, S12, S13, S14, S15, S16, S17, S18, S19, S20, S21, S22, S23, S24, S25, S26, S27, S28, S29, S30, S31, S32, S33, S34, S35, S36, S37, S38, S39, S40: PG1350

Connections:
GND: B1.1, MCU1.2, MCU1.15, MCU1.16
P0: D2.1, D5.1, D8.1, D11.1, D14.1, D22.1, D25.1, D28.1, D31.1, D34.1, MCU1.14
P1: D3.1, D6.1, D9.1, D12.1, D15.1, D23.1, D26.1, D29.1, D32.1, D35.1, MCU1.13
P2: D1.1, D4.1, D7.1, D10.1, D13.1, D21.1, D24.1, D27.1, D30.1, D33.1, MCU1.17
P3: D16.1, D17.1, D18.1, D19.1, D20.1, D36.1, D37.1, D38.1, D39.1, D40.1, MCU1.18
P4: MCU1.19, S21.2, S22.2, S23.2, S36.2
P5: MCU1.20, S24.2, S25.2, S26.2, S37.2
P6: MCU1.21, S27.2, S28.2, S29.2, S38.2
P7: MCU1.22, S30.2, S31.2, S32.2, S39.2
P8: MCU1.23, S33.2, S34.2, S35.2, S40.2
P14: MCU1.10, S10.2, S11.2, S12.2, S19.2
P15: MCU1.9, S7.2, S8.2, S9.2, S18.2
P16: MCU1.11, S13.2, S14.2, S15.2, S20.2
P18: MCU1.8, S4.2, S5.2, S6.2, S17.2
P19: MCU1.7, S1.2, S2.2, S3.2, S16.2
RST: B1.2, MCU1.3
c1_r1: D1.2, S1.1
c1_r2: D2.2, S2.1
c1_r3: D3.2, S3.1
c1_rt: D16.2, S16.1
c1m_r1: D21.2, S21.1
c1m_r2: D22.2, S22.1
c1m_r3: D23.2, S23.1
c1m_rt: D36.2, S36.1
c2_r1: D4.2, S4.1
c2_r2: D5.2, S5.1
c2_r3: D6.2, S6.1
c2_rt: D17.2, S17.1
c2m_r1: D24.2, S24.1
c2m_r2: D25.2, S25.1
c2m_r3: D26.2, S26.1
c2m_rt: D37.2, S37.1
c3_r1: D7.2, S7.1
c3_r2: D8.2, S8.1
c3_r3: D9.2, S9.1
c3_rt: D18.2, S18.1
c3m_r1: D27.2, S27.1
c3m_r2: D28.2, S28.1
c3m_r3: D29.2, S29.1
c3m_rt: D38.2, S38.1
c4_r1: D10.2, S10.1
c4_r2: D11.2, S11.1
c4_r3: D12.2, S12.1
c4_rt: D19.2, S19.1
c4m_r1: D30.2, S30.1
c4m_r2: D31.2, S31.1
c4m_r3: D32.2, S32.1
c4m_rt: D39.2, S39.1
c5_r1: D13.2, S13.1
c5_r2: D14.2, S14.1
c5_r3: D15.2, S15.1
c5_rt: D20.2, S20.1
c5m_r1: D33.2, S33.1
c5m_r2: D34.2, S34.1
c5m_r3: D35.2, S35.1
c5m_rt: D40.2, S40.1

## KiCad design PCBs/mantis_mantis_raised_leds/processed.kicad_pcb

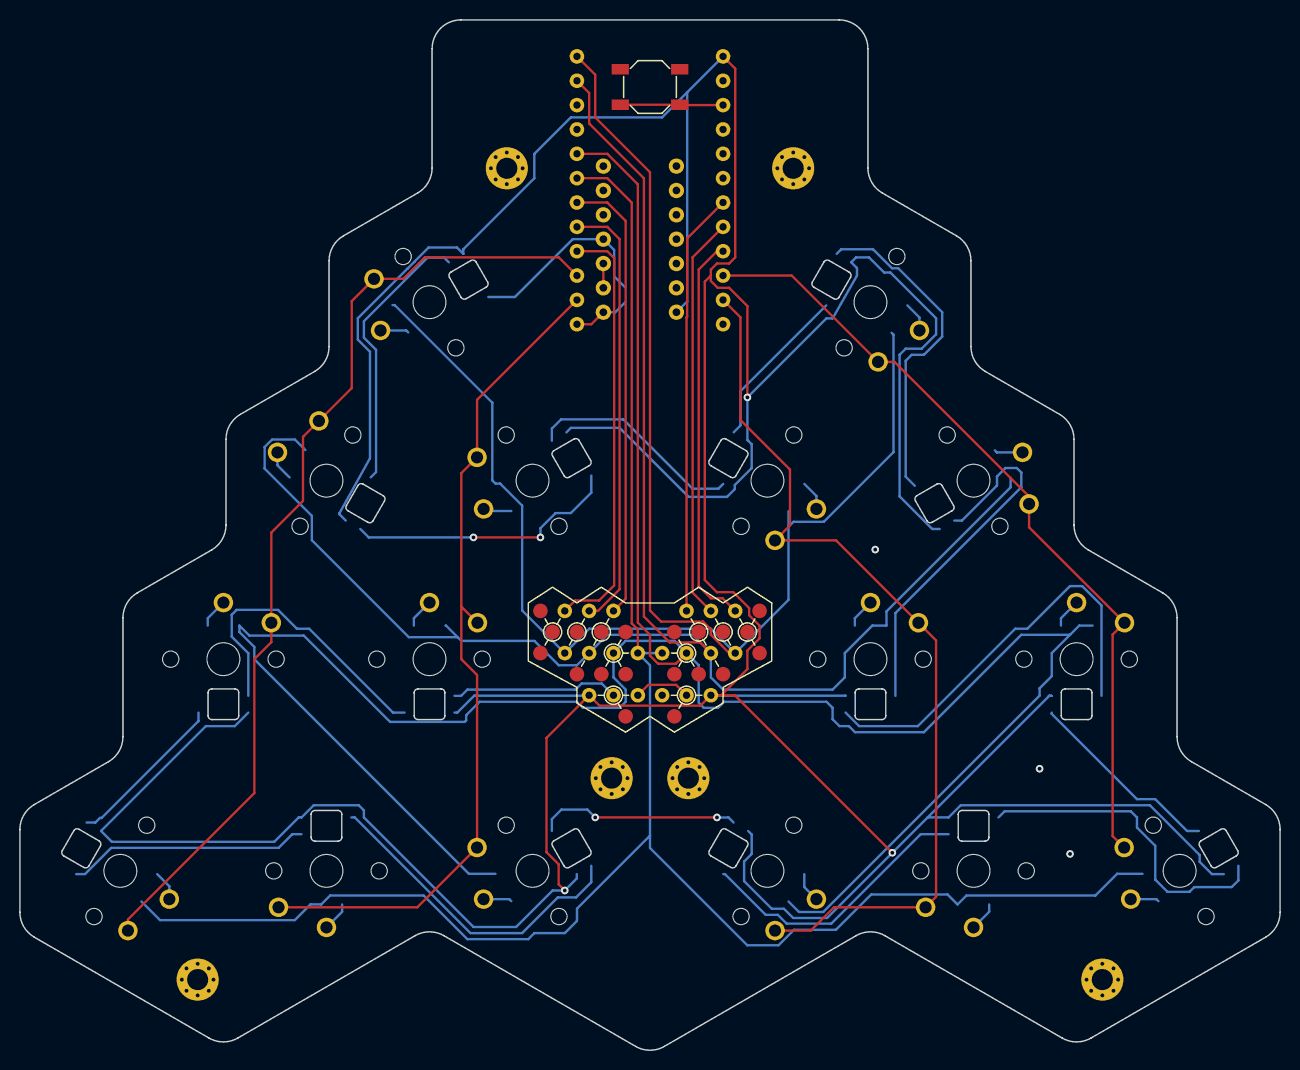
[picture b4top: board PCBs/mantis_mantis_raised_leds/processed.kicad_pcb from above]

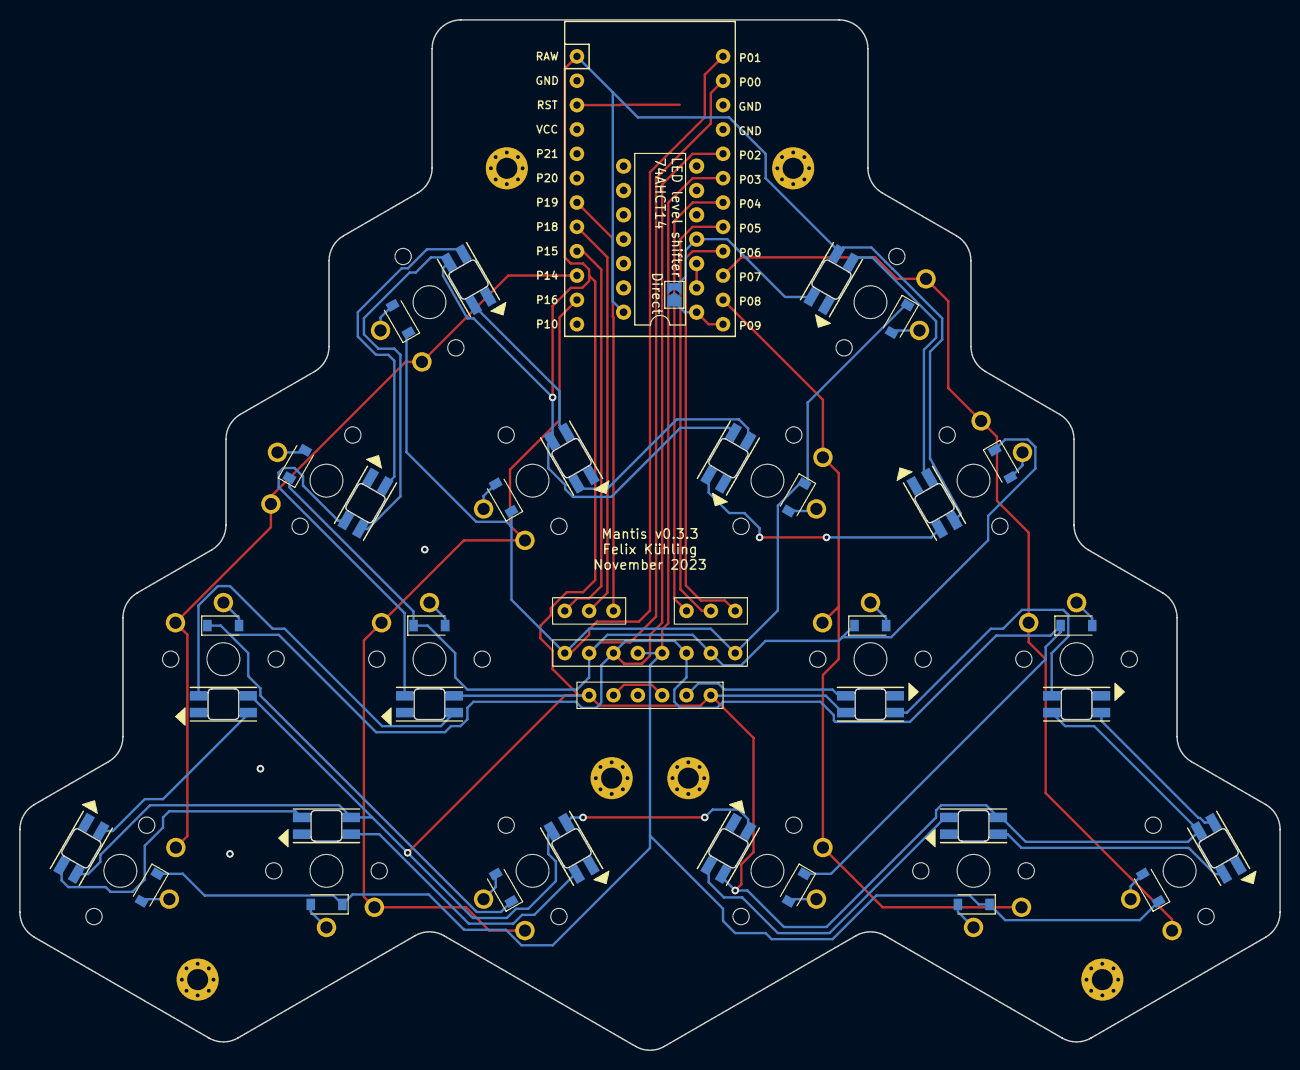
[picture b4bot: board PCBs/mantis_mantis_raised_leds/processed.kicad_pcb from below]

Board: 2 copper layers, 131.5 x 107.5 mm, 59 parts (2 on the bottom side), 52 nets.

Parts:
B1: SW_TACT_ALPS_SKQGABE010
D1, D2, D3, D4, D5, D6, D7, D8, D9, D10, D11, D12, D13, D14, D15, D16: SOD123-back
Direct: SolderJumper-2_P1.3mm_Open_TrianglePad1.0x1.5mm
LED1, LED2, LED3, LED4, LED5, LED6, LED7, LED8, LED9, LED10, LED11, LED12, LED13, LED14, LED15, LED16: SK6812_MINI-E-back
LED level shifter: DIP-14_W7.62mm
MCU1: ProMicro-back
MCU2: Connector-20pin
PAD1, PAD2, PAD3, PAD4, PAD5, PAD6: MountingHole_2.2mm_M2_Pad_Via
S1, S2, S3, S4, S5, S6, S7, S8, S9, S10, S11, S12, S13, S14, S15, S16: PG1350

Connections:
C1: MCU1.19, MCU2.19
C2: MCU1.20, MCU2.20
C3: MCU1.21, MCU2.21
C4: MCU1.22, S1.1, S3.1, S5.1, S7.1
C5: MCU1.23, S2.1, S4.1, S6.1, S8.1
GND: B1.1, LED1.3, LED2.3, LED3.3, LED4.3, LED5.3, LED6.3, LED7.3, LED8.3, LED9.3, LED10.3, LED11.3, LED12.3, LED13.3, LED14.3, LED15.3, LED16.3, LED level shifter.7, MCU1.2, MCU1.15, MCU1.16, PAD1.1, PAD2.1, PAD3.1, PAD4.1, PAD5.1, PAD6.1
LED: Direct.1, LED level shifter.1, MCU1.24
M_C1: MCU1.7, MCU2.7
M_C2: MCU1.8, MCU2.8
M_C3: MCU1.9, MCU2.9
M_C4: MCU1.10, S9.1, S11.1, S13.1, S15.1
M_C5: MCU1.11, S10.1, S12.1, S14.1, S16.1
R1: D5.1, D6.1, D13.1, D14.1, MCU1.17, MCU2.10, MCU2.17
R2: D3.1, D4.1, D11.1, D12.1, MCU1.14, MCU2.6, MCU2.14
R3: D1.1, D2.1, D9.1, D10.1, MCU1.13, MCU2.5, MCU2.13
RST: B1.2, MCU1.3
RT: D7.1, D8.1, D15.1, D16.1, MCU1.18, MCU2.11, MCU2.18
VCC: LED1.1, LED2.1, LED3.1, LED4.1, LED5.1, LED6.1, LED7.1, LED8.1, LED9.1, LED10.1, LED11.1, LED12.1, LED13.1, LED14.1, LED15.1, LED16.1, LED level shifter.14, MCU1.1, MCU2.4, MCU2.22
c4_r1: D5.2, S5.2
c4_r2: D3.2, S3.2
c4_r3: D1.2, S1.2
c4_rt: D7.2, S7.2
c5_r1: D6.2, S6.2
c5_r2: D4.2, S4.2
c5_r3: D2.2, S2.2
c5_rt: D8.2, S8.2
di_c4_r1: LED5.4, LED7.2
di_c4_r2: LED1.2, LED3.4
di_c4_r3: Direct.2, LED1.4, LED level shifter.4
di_c4_rt: LED7.4, LED8.2
di_c5_r1: LED6.4, LED14.2
di_c5_r2: LED4.4, LED5.2
di_c5_r3: LED2.4, LED3.2
di_c5_rt: LED6.2, LED8.4
di_mirror_c3_r3: MCU2.12, MCU2.24
di_mirror_c4_r1: LED12.2, LED13.4
di_mirror_c4_r2: LED9.2, LED11.4
di_mirror_c4_r3: LED9.4, LED10.2
di_mirror_c4_rt: LED13.2, LED15.4
di_mirror_c5_r1: LED14.4, LED16.2
di_mirror_c5_r2: LED11.2, LED12.4
di_mirror_c5_r3: LED2.2, LED10.4
di_mirror_c5_rt: LED15.2, LED16.4
do_c5_r2: LED4.2, MCU2.23
mirror_c4_r1: D13.2, S13.2
mirror_c4_r2: D11.2, S11.2
mirror_c4_r3: D9.2, S9.2
mirror_c4_rt: D15.2, S15.2
mirror_c5_r1: D14.2, S14.2
mirror_c5_r2: D12.2, S12.2
mirror_c5_r3: D10.2, S10.2
mirror_c5_rt: D16.2, S16.2
